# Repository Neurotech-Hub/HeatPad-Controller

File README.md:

# Heat Pad Controller

Battery-powered pad that warms up when someone stands close. The thermo-graphics visible once the pad is warm, and disappears again as the pad cools.

The controller is an Adafruit ESP32-S3 TFT Feather. It reads a time-of-flight distance sensor, turns a boost converter on and off to feed the heat pad, and draws the live distance, battery level, and heart on its screen. There is no temperature sensor. Timing stands in for how hot the pad is.

Firmware source is in [`heatpad_firmware`](heatpad_firmware). That folder’s README covers wiring and how to upload the sketch.

## Firmware settings

You can change how the pad behaves without uploading new code. Type a command in the Serial Monitor and press Enter.

These settings stay programmed even after a reset or a power cycle. The board stores them in flash, so unplugging the battery does not erase them. They stay in place until you send `defaults`, or until you upload a sketch with Arduino’s “Erase all flash before sketch upload” option turned on.

| Setting | What it does | Factory value |
| --- | --- | --- |
| `heat` | How long the pad stays fully on after someone is first detected. This is the warm-up. | 20000 ms (20 s) |
| `pwm-on` | After the warm-up, the pad pulses to hold temperature. This is how long each pulse stays on. | 100 ms |
| `pwm-off` | How long each pulse stays off. A shorter off time keeps the pad hotter. A longer off time lets it cool more. | 100 ms |
| `near` | Distance at which the pad starts heating. The person must be this close, or closer. | 35 cm |
| `far` | Distance at which the pad turns off. The person must be farther than this. | 40 cm |
| `cool` | After the person walks away, how long the heart on the screen takes to fade. This does not change how fast the paint itself cools. | 10000 ms (10 s) |

`near` has to be a smaller number than `far`. That gap is the difference between “someone stepped in” and “someone walked away.”

Times must be from 50 to 60000 milliseconds. Distances must be from 1 to 200 centimeters. A number outside those limits is rejected, and the old value stays as it was. If a pulse is already running, it finishes the current on or off interval, then uses the new time.

### Commands

| Command           | What it does                                                       |
| ----------------- | ------------------------------------------------------------------ |
| `get`             | Print the settings in use, and whether they were loaded from flash |
| `set heat 15000`  | Set the warm-up time, in milliseconds                              |
| `set pwm-on 500`  | Set the hold pulse on time, in milliseconds                        |
| `set pwm-off 400` | Set the hold pulse off time, in milliseconds                       |
| `set near 35`     | Start heating at or under this distance, in centimeters            |
| `set far 45`      | Stop heating beyond this distance, in centimeters                  |
| `set cool 5000`   | Set how long the on-screen heart takes to fade, in milliseconds    |
| `defaults`        | Put the factory numbers back and erase the saved copy              |
| `help`            | List the commands                                                  |

Pins, how many readings are required before the pad reacts, and the low-battery cutoff live in `heatpad_firmware/config.h`. Those need a new upload to change.

## Bill of materials

| Part | Notes | Link |
| --- | --- | --- |
| Heat pad | Fabric pad warmed by the boost output | [Amazon](https://a.co/d/0cVdlTN0) |
| Time-of-flight sensor | Distance sensor on the Feather STEMMA QT port | [Adafruit 3967](https://www.adafruit.com/product/3967) |
| ESP32-S3 TFT Feather | Controller and display | [Adafruit 5483](https://www.adafruit.com/product/5483) |
| Adjustable boost converter | Pololu 2890. The potentiometer sets the output, up to 20 V. This build uses 5 V. Set and check the voltage with a meter before connecting the pad. | [DigiKey](https://www.digikey.com/en/products/detail/pololu/2890/10451201) |
| Battery | LiPo for the Feather and the boost input | [Adafruit 1781](https://www.adafruit.com/product/1781) |

## Enclosure

The enclosure design is on Autodesk Fusion: [https://a360.co/4A1Bd32](https://a360.co/4A1Bd32)

The circuit board design is in [`KiCAD/Heat_Pad_v1.0`](KiCAD/Heat_Pad_v1.0).

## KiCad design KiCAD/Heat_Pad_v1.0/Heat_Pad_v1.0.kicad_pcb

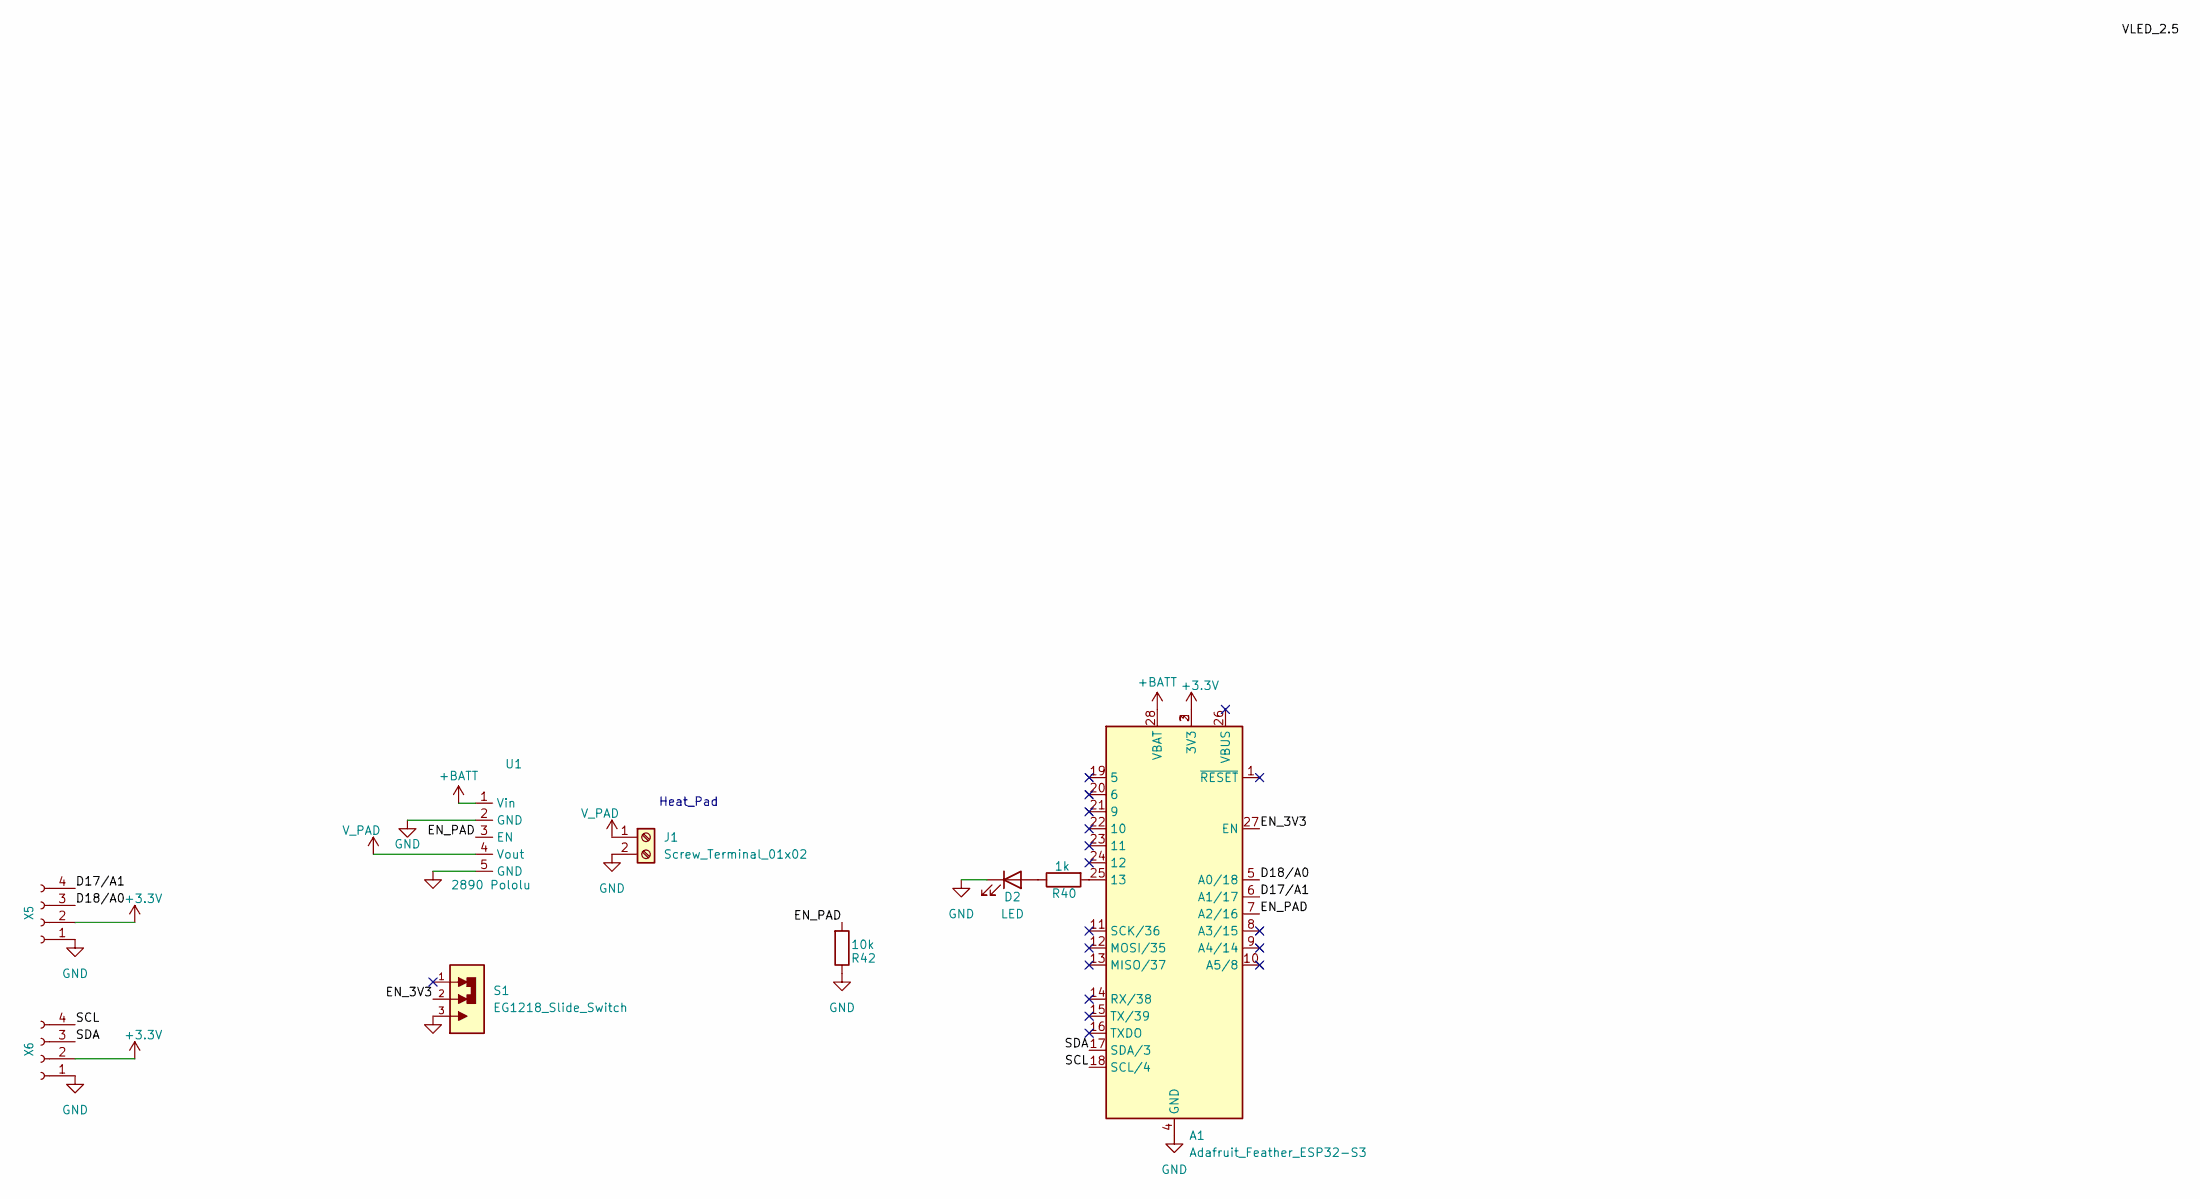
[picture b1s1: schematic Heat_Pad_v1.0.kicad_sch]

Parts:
A1: Adafruit_Feather_ESP32-S3; DigiKey 1528-5483-ND
D2: LED; LED_1206_3216Metric; DigiKey 160-1405-1-ND
J1: Screw_Terminal_01x02; TerminalBlock_Xinya_XY308-2.54-2P_1x02_P2.54mm_Horizontal
R40: 1k; R_0603_1608Metric; LCSC C21190
R42: 10k; R_0603_1608Metric; DigiKey 311-10.0KMCT-ND
S1: EG1218_Slide_Switch; SW_EG1218; DigiKey EG1903-ND
U1: 2890 Pololu; u3v70x_Pololu; DigiKey 2183-2890-ND
X5, X6: JSTPH; X5_JST_SH_SM04B-SRSS-TB_1x04-1MP_P1.00mm_Horizontal; LCSC C160404

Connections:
+3.3V: A1.2 (3V3), A1.3 (3V3), X5.2, X6.2
+12V: J1.1, U1.4 (Vout)
+BATT: A1.28 (VBAT), U1.1 (Vin)
/D9: A1.21 (9)
/D17/A1: A1.6 (A1/17), X5.4
/D18/A0: A1.5 (A0/18), X5.3
/EN_3V3: A1.27 (EN), S1.2
/EN_12V: A1.7 (A2/16), R42.2, U1.3 (EN)
/SCL: A1.18 (SCL/4), X6.4
/SDA: A1.17 (SDA/3), X6.3
GND: A1.4 (GND), D2.1 (K), J1.2, R42.1, S1.3, U1.2 (GND), U1.5 (GND), X5.1, X6.1
unnamed: A1.25 (13), R40.2
unnamed: D2.2 (A), R40.1

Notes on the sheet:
Heat_Pad

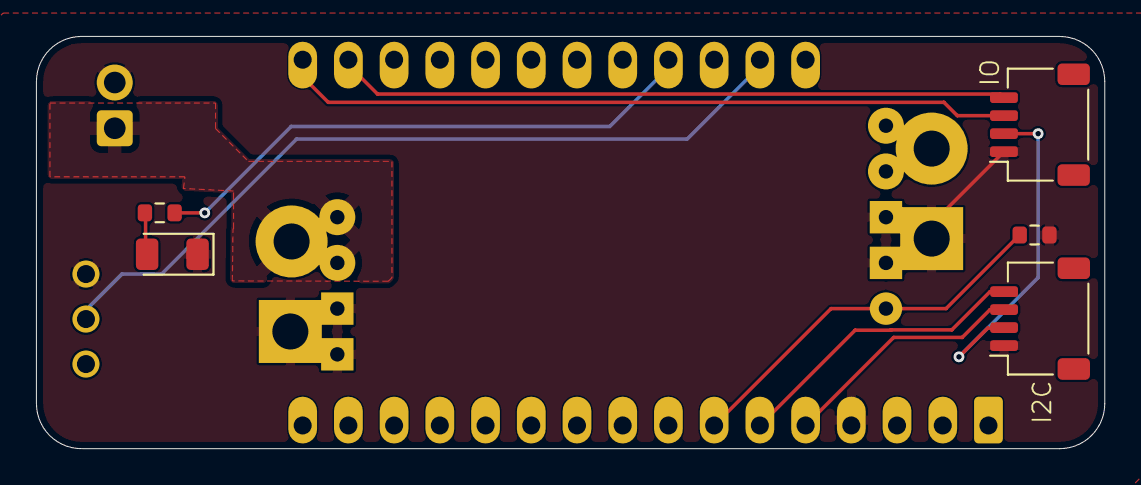
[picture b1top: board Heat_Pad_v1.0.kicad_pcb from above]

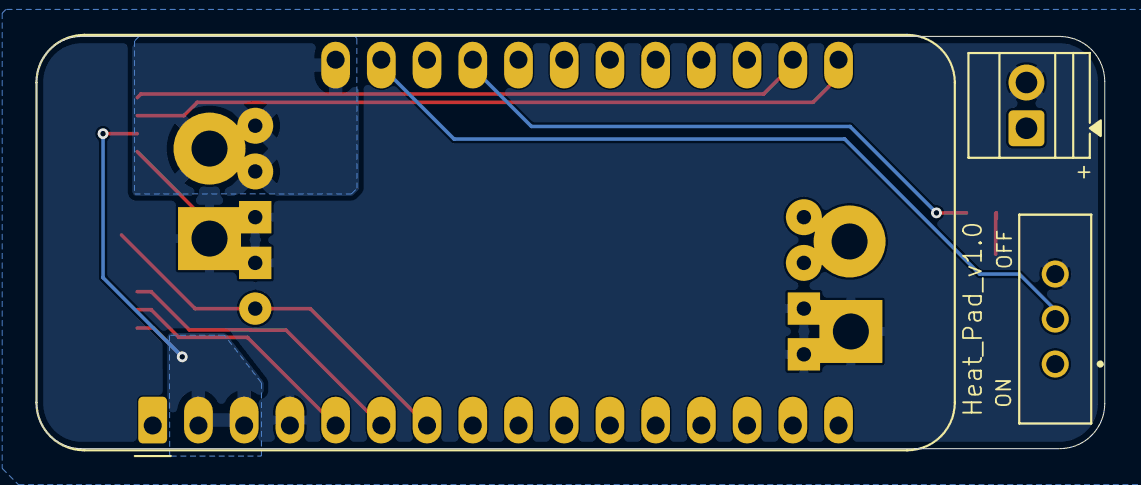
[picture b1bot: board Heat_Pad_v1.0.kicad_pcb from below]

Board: 2 copper layers, 59.3 x 22.9 mm, 9 parts (3 on the bottom side), 12 nets.
